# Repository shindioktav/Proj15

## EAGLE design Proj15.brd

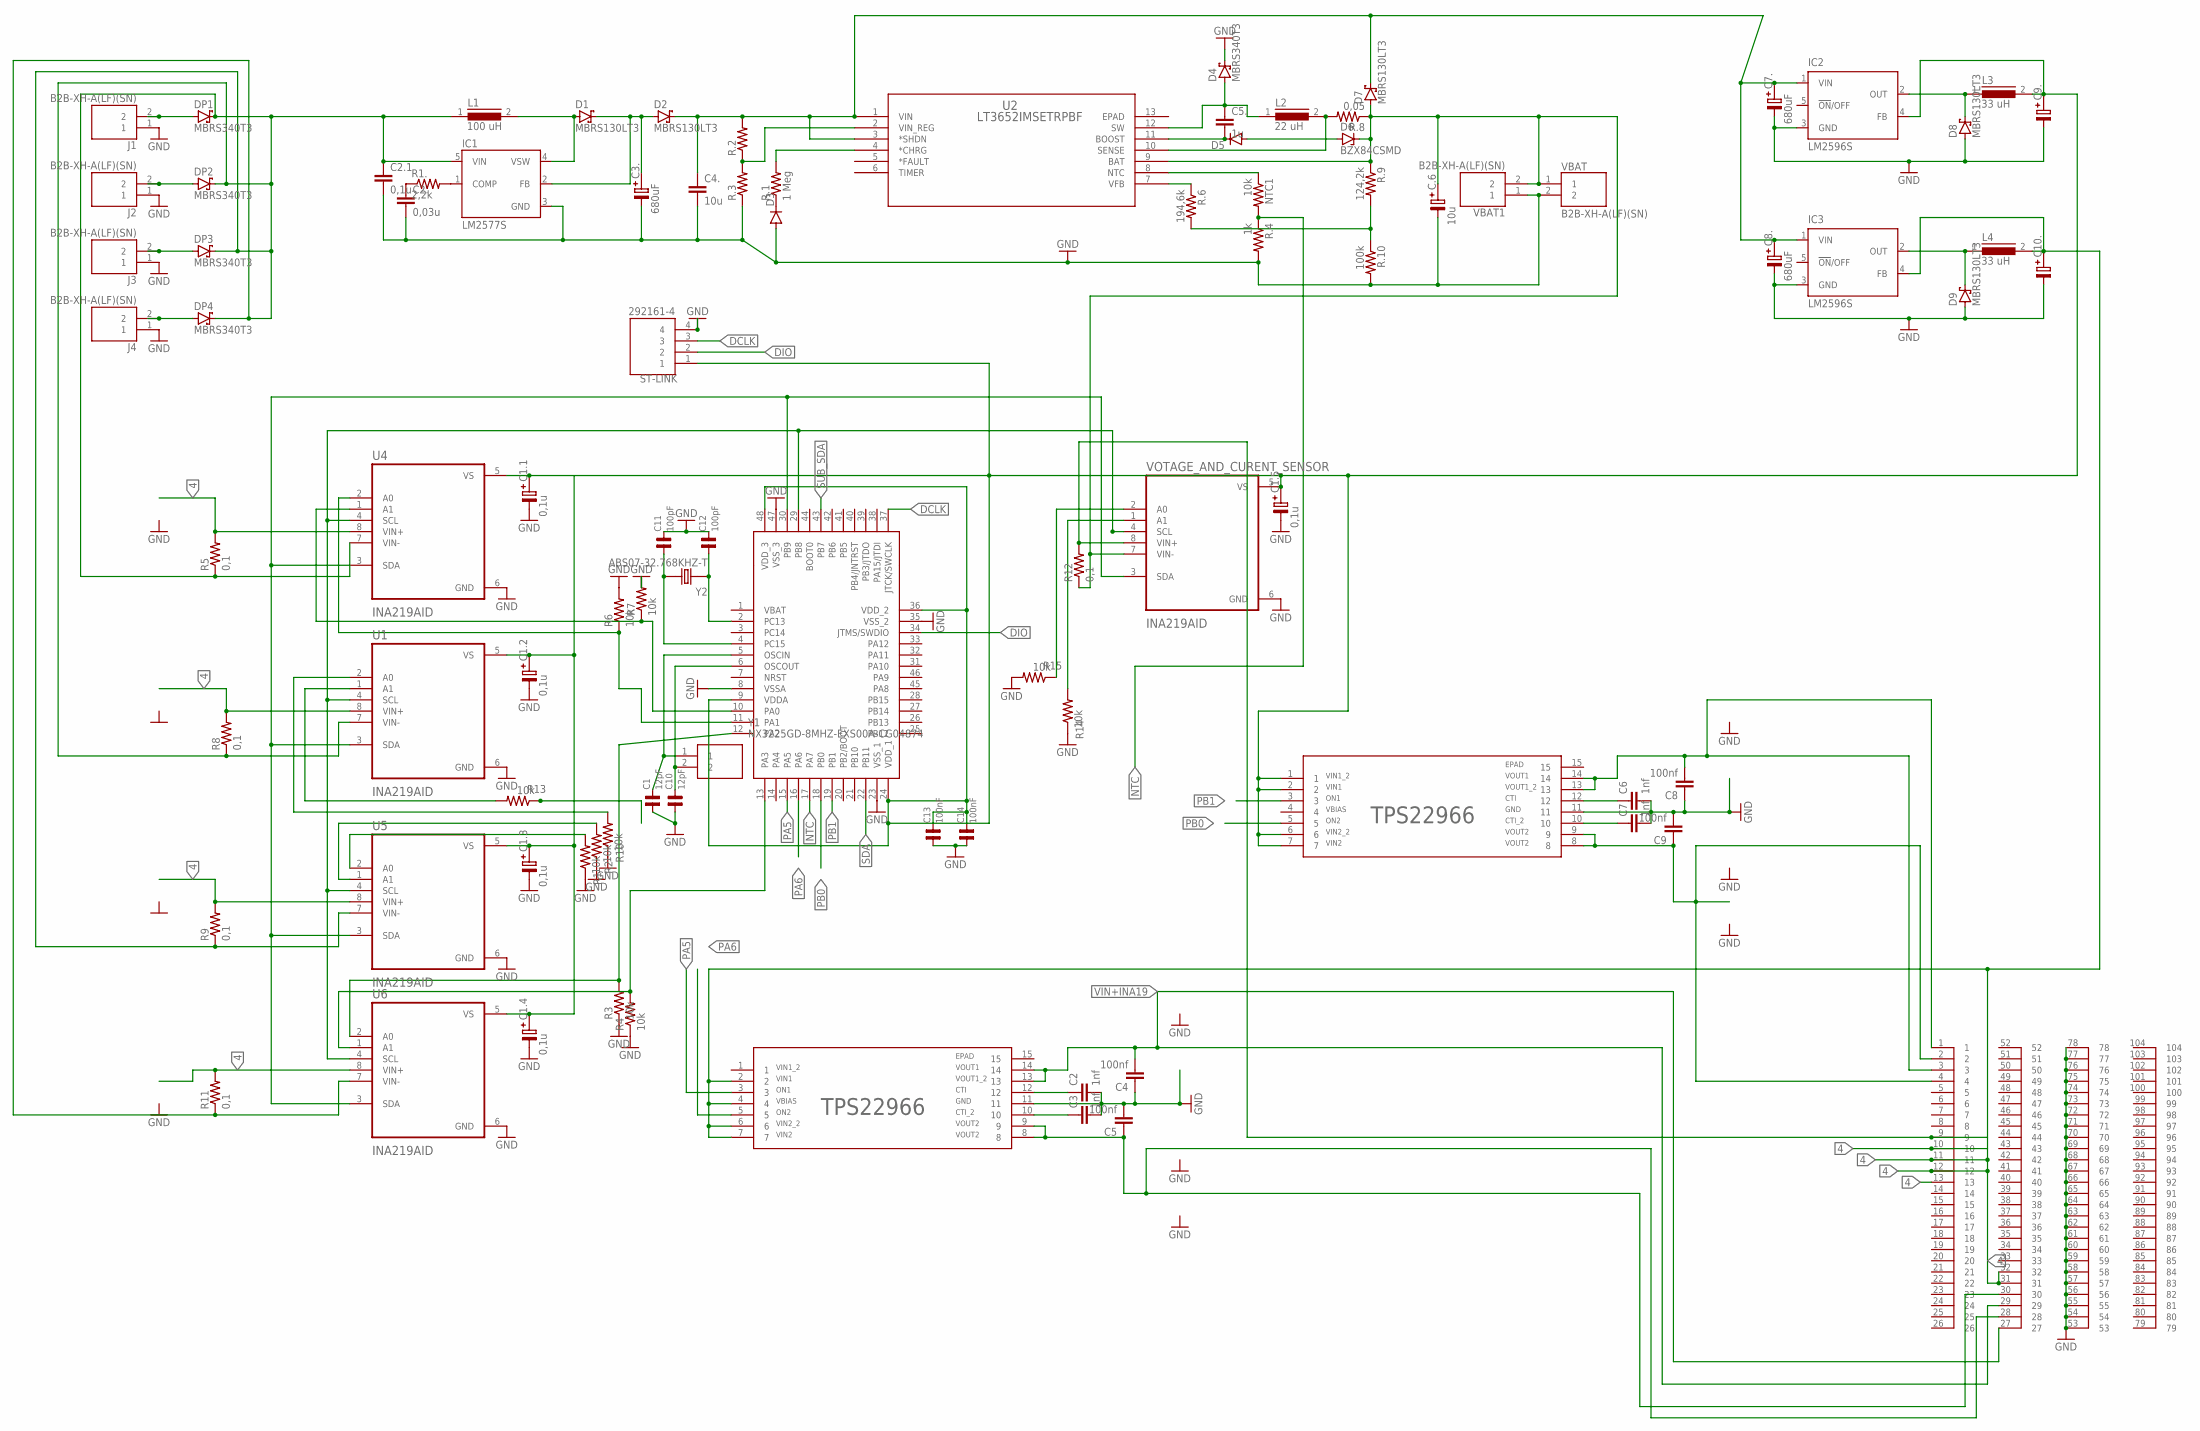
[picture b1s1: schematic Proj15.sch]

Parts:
C1, C10: 12pF; 0805
C1.1, C1.2, C1.3, C1.4, C1.5: 0,1u; TE-D-7343
C2, C3, C6, C7: 1nf; C0805
C2.: 0,03u; C1206
C2.1: 0,1u; C1206
C3., C7., C8.: 680uF; TE-D-7343
C4, C5, C8, C9: 100nf; C0805
C4.: 10u; C1206
C5.: 1u; C1206
C9., C10.: C-PR-SMD-TE-D; TE-D-7343
C11, C12: 100pF; 0805
C13, C14: 100nF; 0805
C.6: 10u; TE-D-7343
D1, D2, D7, D8, D9: MBRS130LT3; SMB
D3, D5: DIODE-DO214BA; DO214BA
D4: MBRS340T3; SMC
D6: BZX84CSMD; TO236
DP1, DP2, DP3, DP4: MBRS340T3; SMC
IC1: LM2577S; TO263-5
IC2, IC3: LM2596S; TO263-5
J1, J2, J3, J4: B2B-XH-A(LF)(SN); JST_B2B-XH-A(LF)(SN)
L1: 100 uH; DR127
L2: 22 uH; DR127
L3, L4: 33 uH; DR127
NTC1: 10k; R0603
R1, R2, R3, R4, R6, R7, R10, R13, R14, R15: 10k; R3216
R1.: 2,2k; R3216
R5, R8, R9, R11, R12: 0,1; R3216
R.1: 1 Meg; R3216
R.2, R.3: R-US_R3216; R3216
R.4: 1k; R3216
R.6: 194,6k; R3216
R.8: 0,05; R3216
R.9: 124,2k; R3216
R.10: 100k; R3216
ST-LINK: 292161-4; TE_292161-4
U1, U4, U5, U6: INA219AID; SOIC127P599X175-8N
U2: LT3652IMSETRPBF; MSOP-12_MSE
U3: QFP50P900X900X160-48N
U$1, U$2: TPS22966; SON40P300X200X80-15N
U$3: HEADERPIN4X26
VBAT, VBAT1: B2B-XH-A(LF)(SN); JST_B2B-XH-A(LF)(SN)
VOTAGE_AND_CURENT_SENSOR: INA219AID; SOIC127P599X175-8N
Y1: NX3225GD-8MHZ-EXS00A-CG04874; NX3225GD-STD-CRA-3
Y2: ABS07-32.768KHZ-T; XTAL_ABS07-32.768KHZ-T

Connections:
4: C10..+, IC3.4 (FB), L4.2, R5.2, R8.2, R9.2, R11.2, R12.2, U1.8 (VIN+), U4.8 (VIN+), U5.8 (VIN+), U6.8 (VIN+), U$1.2, U$1.4, U$1.6, U$1.7, U$3.9, U$3.10, U$3.11, U$3.12, U$3.13, U$3.31, U$3.32, VOTAGE_AND_CURENT_SENSOR.8 (VIN+)
DCLK: ST-LINK.3, U3.37 (JTCK/SWCLK)
DIO: ST-LINK.2, U3.34 (JTMS/SWDIO)
GND: C1.1, C1.1.-, C1.2.-, C1.3.-, C1.4.-, C1.5.-, C2.2, C2..2, C2.1.2, C3.2, C3..-, C4.1, C4..2, C5.2, C6.2, C7.2, C7..-, C8.1, C8..-, C9.2, C9..-, C10.1, C10..-, C11.2, C12.2, C13.1, C14.1, C.6.-, D3.A, D4.C, D8.A, D9.A, IC1.3 (GND), IC2.3 (GND), IC3.3 (GND), J1.1, J2.1, J3.1, J4.1, R1.1, R2.1, R3.1, R4.1, R6.2, R7.2, R10.1, R14.1, R15.2, R.3.1, R.4.2, R.10.2, ST-LINK.4, U1.6 (GND), U3.8 (VSSA), U3.23 (VSS_1), U3.35 (VSS_2), U3.47 (VSS_3), U4.6 (GND), U5.6 (GND), U6.6 (GND), U$1.11, U$2.11, U$3.53, U$3.54, U$3.55, U$3.56, U$3.57, U$3.58, U$3.59, U$3.60, U$3.61, U$3.62, U$3.63, U$3.64, U$3.65, U$3.66, U$3.67, U$3.68, U$3.69, U$3.70, U$3.71, U$3.72, U$3.73, U$3.74, U$3.75, U$3.76, U$3.77, U$3.78, VBAT.2, VBAT1.1, VOTAGE_AND_CURENT_SENSOR.6 (GND)
unnamed: R10.2, U1.2 (A0)
unnamed: U1.4 (SCL), U3.29 (PB8), U4.4 (SCL), U5.4 (SCL), U6.4 (SCL), VOTAGE_AND_CURENT_SENSOR.4 (SCL)
unnamed: R1.2, U5.2 (A0)
unnamed: R2.2, U5.1 (A1)
unnamed: R3.2, U3.12 (PA2), U6.2 (A0)
unnamed: R4.2, U3.13 (PA3), U6.1 (A1)
unnamed: R6.1, U3.11 (PA1), U4.2 (A0)
unnamed: R7.1, U3.10 (PA0), U4.1 (A1)
unnamed: C8.2, U$2.13, U$2.14, U$3.1, U$3.3
unnamed: U1.3 (SDA), U3.30 (PB9), U4.3 (SDA), U5.3 (SDA), U6.3 (SDA), VOTAGE_AND_CURENT_SENSOR.3 (SDA)
unnamed: R15.1, VOTAGE_AND_CURENT_SENSOR.2 (A0)
unnamed: C12.1, U3.2 (PC13), Y2.1
unnamed: C2.1, U$1.12
unnamed: C3.1, U$1.10
unnamed: C5.1, U$1.8, U$1.9, U$3.28, U$3.30
unnamed: C10.2, U3.6 (OSCOUT), Y1.2
unnamed: C6.1, U$2.12
unnamed: C7.1, U$2.10
unnamed: C1.2, U3.5 (OSCIN), Y1.1
unnamed: C9.1, U$2.8, U$2.9, U$3.2, U$3.4
unnamed: C11.1, U3.4 (PC15), Y2.2
unnamed: D8.C, IC2.2 (OUT), L3.1
unnamed: DP2.A, J2.2
unnamed: DP3.A, J3.2
unnamed: DP4.A, J4.2
unnamed: DP1.A, J1.2
unnamed: D1.A, IC1.4 (VSW), L1.2
unnamed: C3..+, D1.C, D2.A, IC1.2 (FB)
unnamed: IC1.1 (COMP), R1..2
unnamed: R13.2, U1.1 (A1)
unnamed: C2..1, R1..1
unnamed: C4..1, C7..+, C8..+, D2.C, D7.C, IC2.1 (VIN), IC3.1 (VIN), R.2.2, U2.1 (VIN), U2.3 (*SHDN)
unnamed: R.2.1, R.3.2, U2.2 (VIN_REG)
unnamed: D3.C, R.1.1
unnamed: R.1.2, U2.4 (*CHRG)
unnamed: C5..2, D5.C, U2.11 (BOOST)
unnamed: C5..1, D4.A, L2.1, U2.12 (SW)
unnamed: L2.2, R.8.2, U2.10 (SENSE)
unnamed: R.6.1, U2.7 (VFB)
unnamed: D5.A, D6.A
unnamed: C.6.+, D6.C, D7.A, R12.1, R.8.1, R.9.1, U2.9 (BAT), VBAT.1, VBAT1.2, VOTAGE_AND_CURENT_SENSOR.7 (VIN-)
unnamed: NTC1.1, U2.8 (NTC)
unnamed: R.6.2, R.9.2, R.10.1
unnamed: C1.1.+, C1.2.+, C1.3.+, C1.4.+, C1.5.+, C9..+, C13.2, C14.2, IC2.4 (FB), L3.2, ST-LINK.1, U1.5 (VS), U3.9 (VDDA), U3.24 (VDD_1), U3.36 (VDD_2), U3.48 (VDD_3), U4.5 (VS), U5.5 (VS), U6.5 (VS), U$2.1, U$2.2, U$2.6, U$2.7, VOTAGE_AND_CURENT_SENSOR.5 (VS)
unnamed: D9.C, IC3.2 (OUT), L4.1
unnamed: C2.1.1, DP1.C, DP2.C, DP3.C, DP4.C, IC1.5 (VIN), L1.1, R5.1, R8.1, R9.1, R11.1, U1.7 (VIN-), U4.7 (VIN-), U5.7 (VIN-), U6.7 (VIN-)
NTC: NTC1.2, R14.2, R.4.1, U3.17 (PA7), VOTAGE_AND_CURENT_SENSOR.1 (A1)
PA5: U3.15 (PA5), U$1.3
PA6: U3.16 (PA6), U$1.5
PB0: U3.18 (PB0), U$2.5
PB1: U3.19 (PB1), U$2.3
SDA: U3.22 (PB11)
SUB_SDA: U3.43 (PB7)
VIN+INA19: C4.2, U$1.13, U$1.14, U$3.27, U$3.29

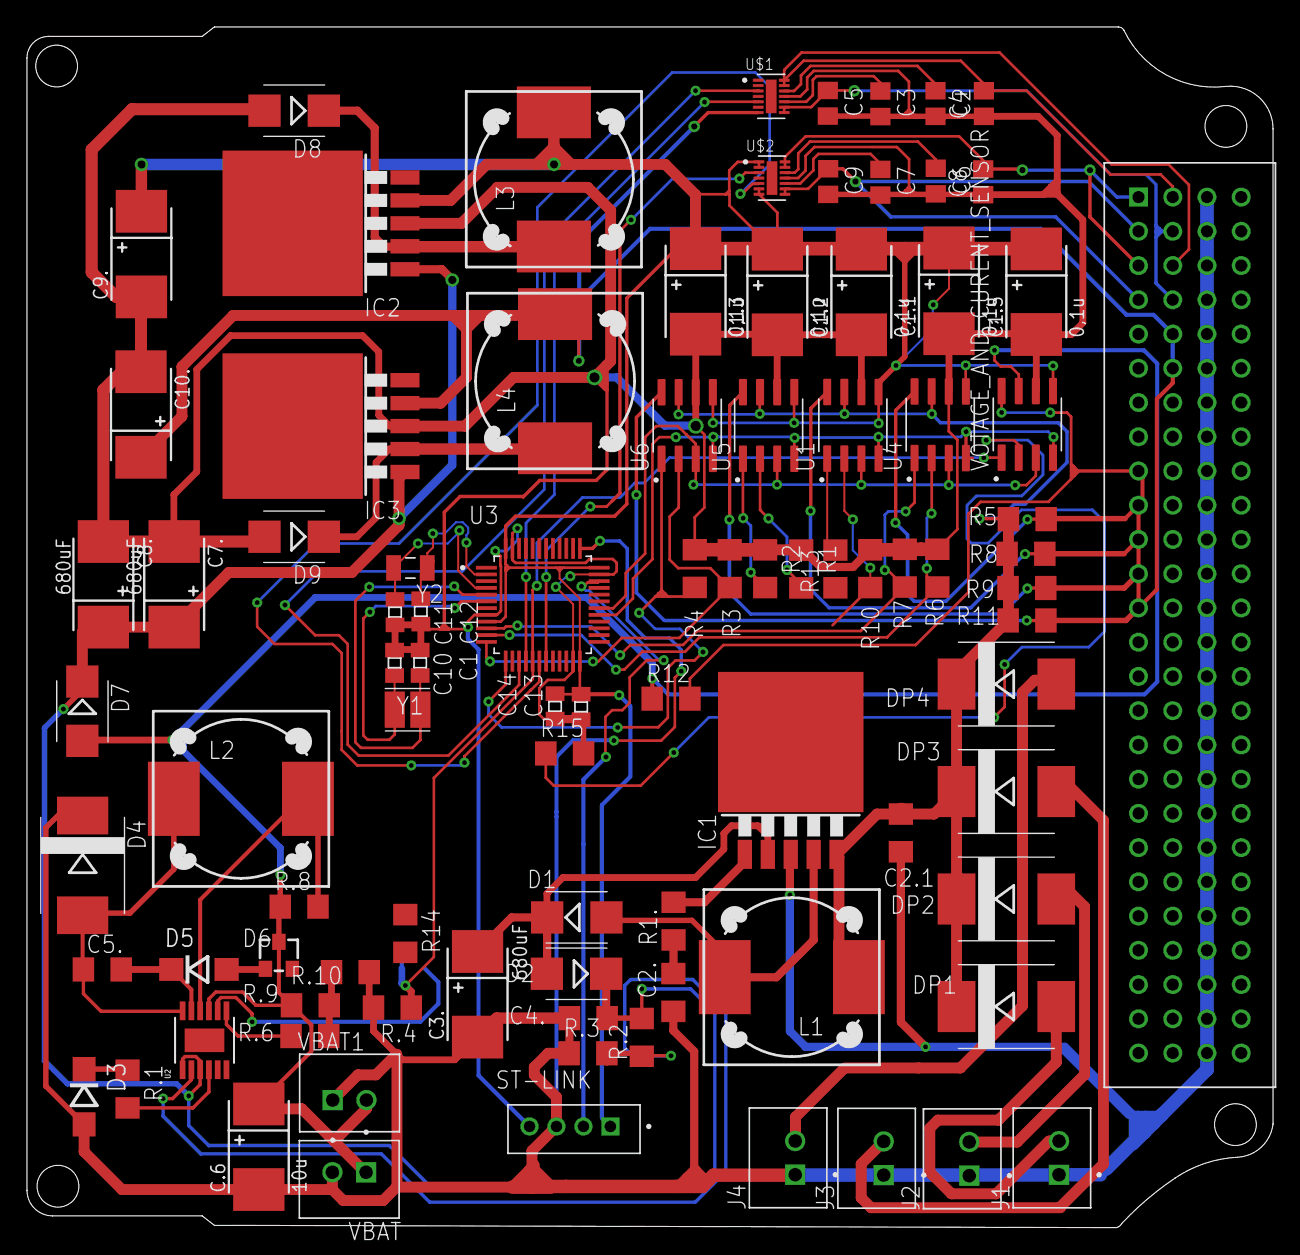
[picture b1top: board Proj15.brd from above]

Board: 2 copper layers, 92.4 x 89.1 mm, 93 parts (1 on the bottom side), 56 nets.

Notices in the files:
parts and their libraries:
cap-pan40: Copyright (C) 2004, Bob Starr
